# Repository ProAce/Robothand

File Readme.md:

# Robothand

This is the coming together of a project that has been lying on the shelf for 5 years. When a buddy and I had to do a school project to graduate we decided to build a robothand that would wirelessly mimic our own hand movement. This made to be a bit of a far stretch for two inexperienced 16 year olds, but we got pretty far. After deciding that the flex sensors we wanted to use where too expensive (10€ a piece) we found a way to make them ourselves. Eventually we couldn't get it too work wirelessly, but it did work wired... kinda.

Now I figured this was something that had to be finished, and with a little more budget and knowledge this time it is coming together quite nicely.

For testing purposes I used a arduino nano I had lying around as a I2C ADC for the ESP8266 board. The hardware design in this repository utilises an ADC128D818 unit which you could order assembled from services like JLCPCB but is also solderable by hand.

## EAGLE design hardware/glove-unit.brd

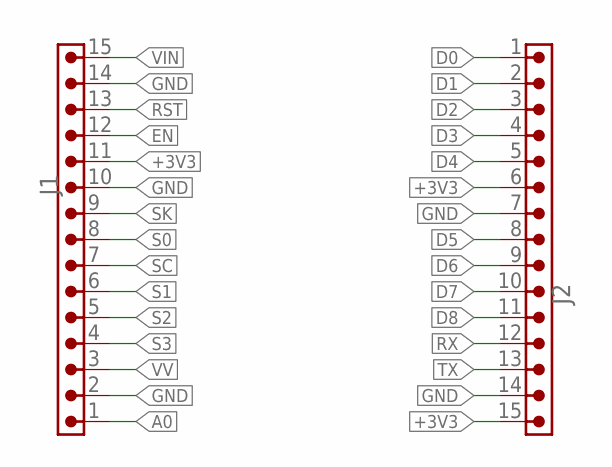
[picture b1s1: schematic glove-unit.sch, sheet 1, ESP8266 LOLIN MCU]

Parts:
J1, J2: 6130XX11121_61301511121; 61301511121

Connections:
+3V3: J1.11, J2.6, J2.15; also elsewhere on the board
A0: J1.1
D0: J2.1
D1: J2.2; also elsewhere on the board
D2: J2.3; also elsewhere on the board
D3: J2.4
D4: J2.5
D5: J2.8
D6: J2.9
D7: J2.10
D8: J2.11
EN: J1.12
GND: J1.2, J1.10, J1.14, J2.7, J2.14; also elsewhere on the board
RST: J1.13
RX: J2.12
S0: J1.8
S1: J1.6
S2: J1.5
S3: J1.4
SC: J1.7
SK: J1.9
TX: J2.13
VIN: J1.15; also elsewhere on the board
VV: J1.3

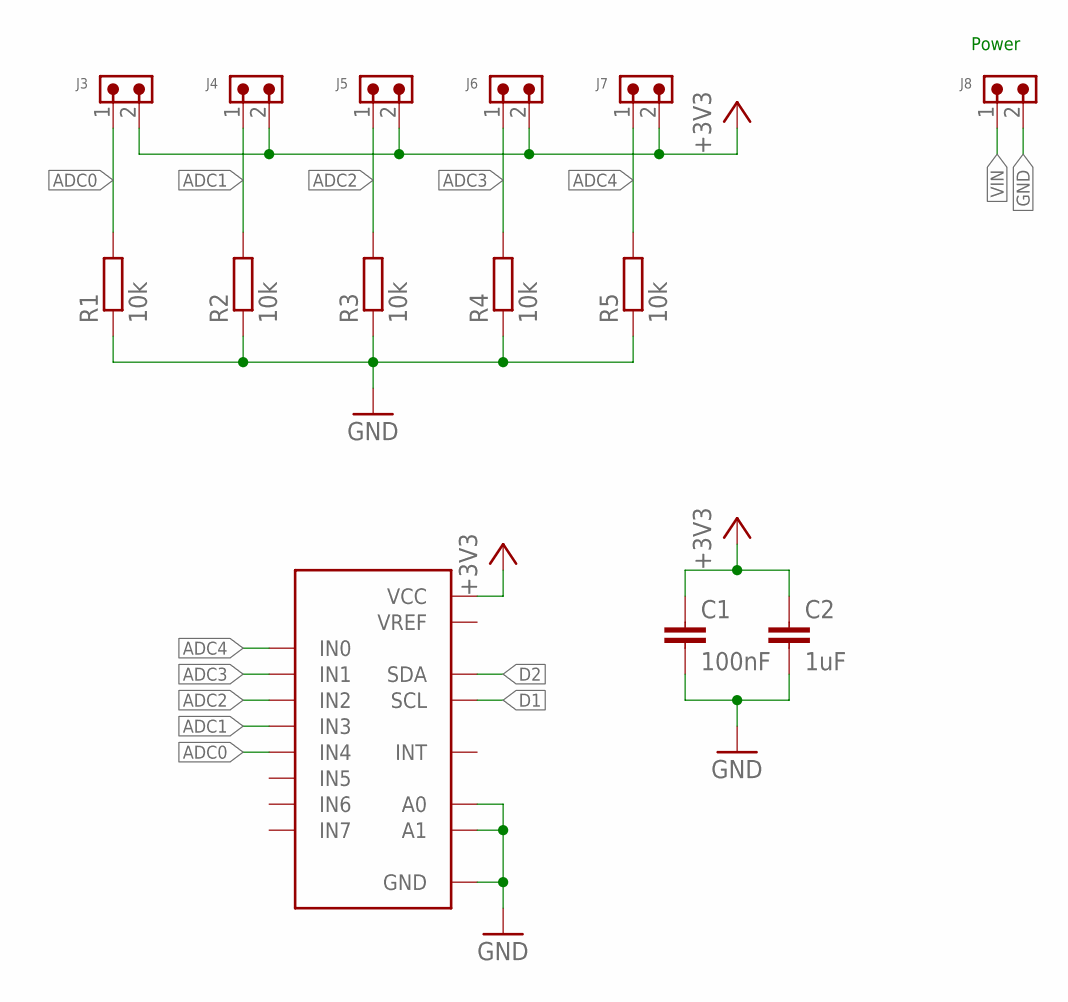
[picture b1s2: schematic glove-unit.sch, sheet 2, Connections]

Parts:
C1: 100nF; C0603
C2: 1uF; C0603
J3, J4, J5, J6, J7, J8: 6130XX11121_61300211121; 61300211121
R1, R2, R3, R4, R5: 10k; R0805
U$1: ADC128D818; TSSOP-16

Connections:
+3V3: C1.1, C2.1, J3.2, J4.2, J5.2, J6.2, J7.2, U$1.5 (VCC); also elsewhere on the board
ADC0: J3.1, R1.2, U$1.12 (IN4)
ADC1: J4.1, R2.2, U$1.13 (IN3)
ADC2: J5.1, R3.2, U$1.14 (IN2)
ADC3: J6.1, R4.2, U$1.15 (IN1)
ADC4: J7.1, R5.2, U$1.16 (IN0)
D1: U$1.3 (SCL); also elsewhere on the board
D2: U$1.2 (SDA); also elsewhere on the board
GND: C1.2, C2.2, J8.2, R1.1, R2.1, R3.1, R4.1, R5.1, U$1.4 (GND), U$1.7 (A0), U$1.8 (A1); also elsewhere on the board
VIN: J8.1; also elsewhere on the board

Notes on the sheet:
Power

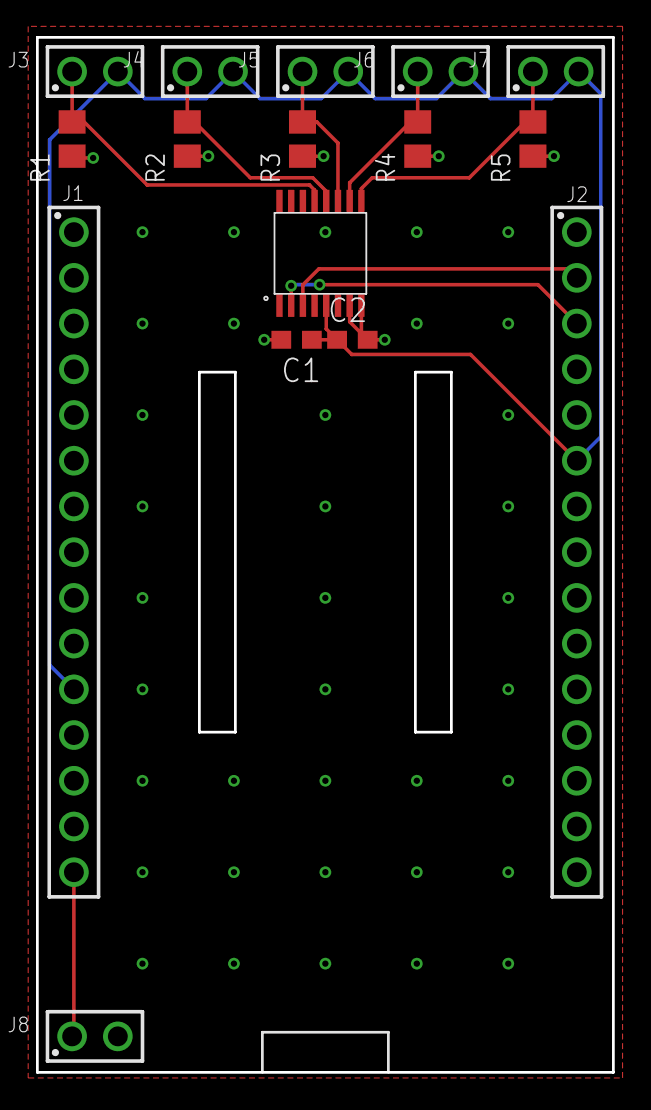
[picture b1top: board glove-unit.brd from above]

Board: 2 copper layers, 32.0 x 57.5 mm, 16 parts (0 on the bottom side), 10 nets.

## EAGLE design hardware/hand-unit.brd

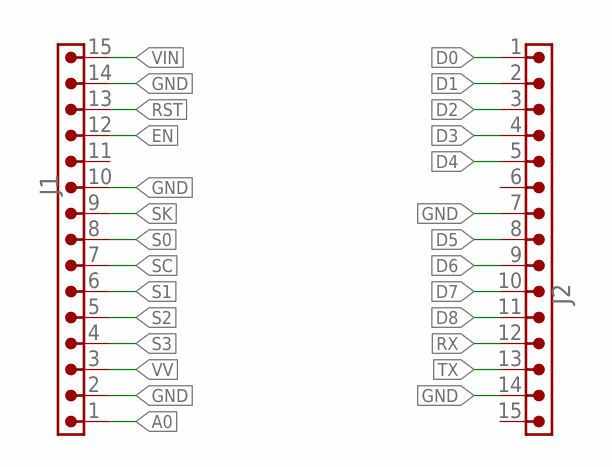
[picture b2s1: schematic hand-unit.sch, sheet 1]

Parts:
J1, J2: 6130XX11121_61301511121; 61301511121

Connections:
A0: J1.1
D0: J2.1; also elsewhere on the board
D1: J2.2
D2: J2.3; also elsewhere on the board
D3: J2.4
D4: J2.5
D5: J2.8; also elsewhere on the board
D6: J2.9; also elsewhere on the board
D7: J2.10; also elsewhere on the board
D8: J2.11
EN: J1.12
GND: J1.2, J1.10, J1.14, J2.7, J2.14; also elsewhere on the board
RST: J1.13
RX: J2.12
S0: J1.8
S1: J1.6
S2: J1.5
S3: J1.4
SC: J1.7
SK: J1.9
TX: J2.13
VIN: J1.15; also elsewhere on the board
VV: J1.3

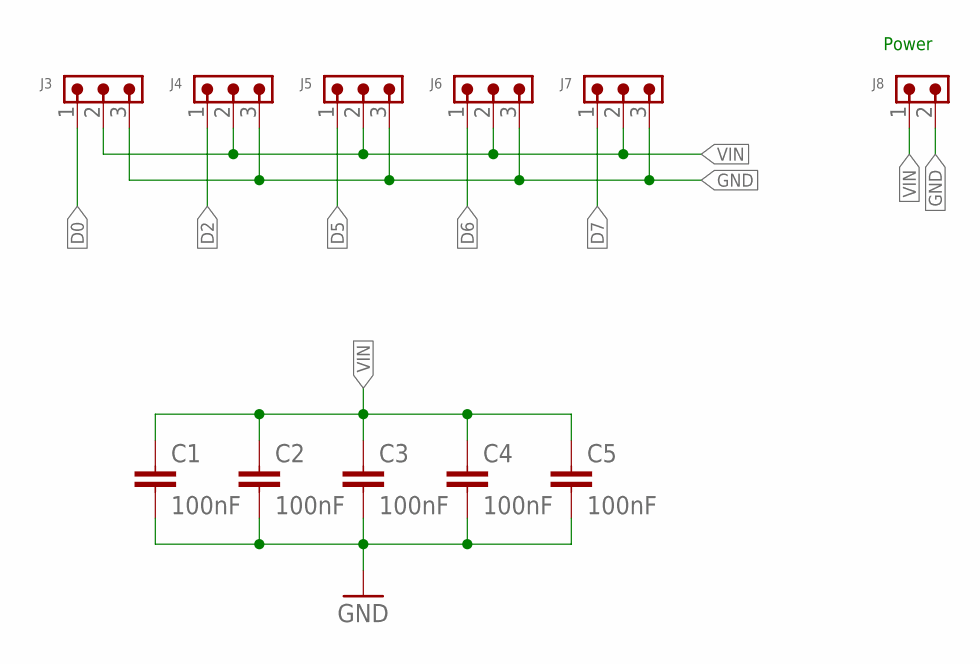
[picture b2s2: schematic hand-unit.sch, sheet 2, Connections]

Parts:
C1, C2, C3, C4, C5: 100nF; C0603
J3, J4, J5, J6, J7: 6130XX11121_61300311121; 61300311121
J8: 6130XX11121_61300211121; 61300211121

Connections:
D0: J3.1; also elsewhere on the board
D2: J4.1; also elsewhere on the board
D5: J5.1; also elsewhere on the board
D6: J6.1; also elsewhere on the board
D7: J7.1; also elsewhere on the board
GND: C1.2, C2.2, C3.2, C4.2, C5.2, J3.3, J4.3, J5.3, J6.3, J7.3, J8.2; also elsewhere on the board
VIN: C1.1, C2.1, C3.1, C4.1, C5.1, J3.2, J4.2, J5.2, J6.2, J7.2, J8.1; also elsewhere on the board

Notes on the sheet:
Power

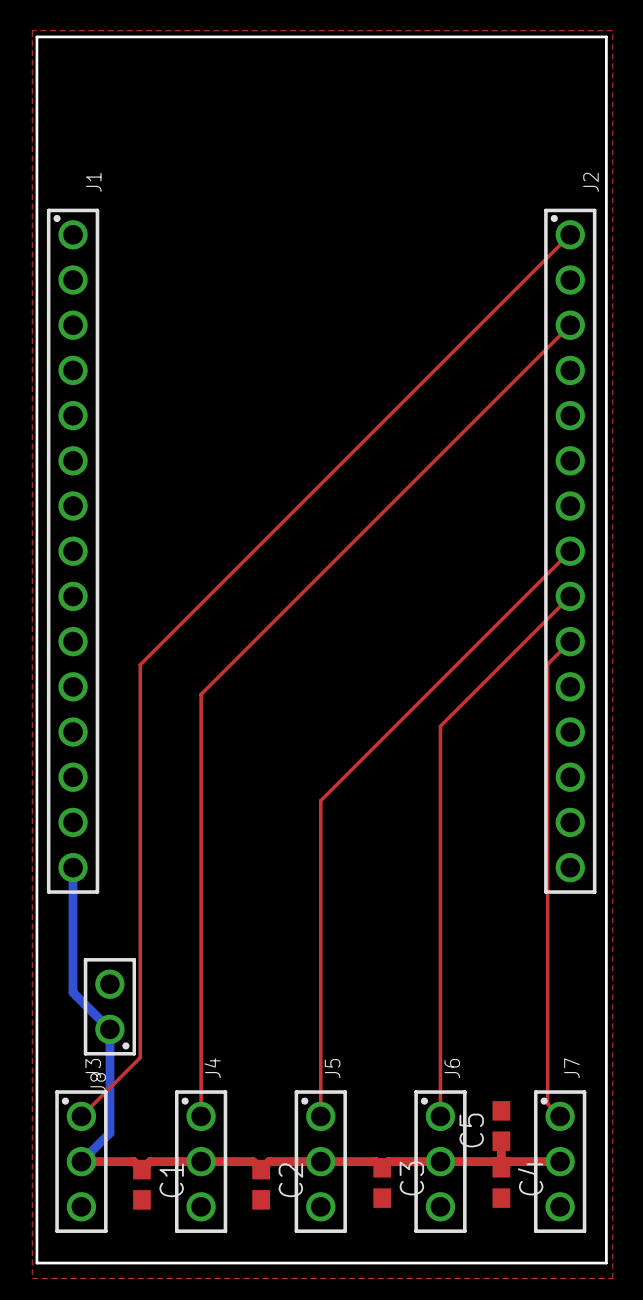
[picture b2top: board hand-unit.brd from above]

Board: 2 copper layers, 32.0 x 68.9 mm, 13 parts (0 on the bottom side), 7 nets.

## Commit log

2020-06-01 add hardware
2020-06-09 ongoing dev
2020-06-09 add websocket server
2020-06-09 Remove sketchy adc thingy
2020-06-09 remove unused JSON parser
2020-06-09 remove server
2020-06-09 actually start listening
2020-06-09 send websocket messages
2020-07-14 Add gitignore
2020-07-14 remove adc hack
2020-07-14 Add webpage for better control
2020-07-14 rework for websockets

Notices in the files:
parts and their libraries:
Wurth_Connectors_WR-PHD: Copyright: Würth Elektronik
